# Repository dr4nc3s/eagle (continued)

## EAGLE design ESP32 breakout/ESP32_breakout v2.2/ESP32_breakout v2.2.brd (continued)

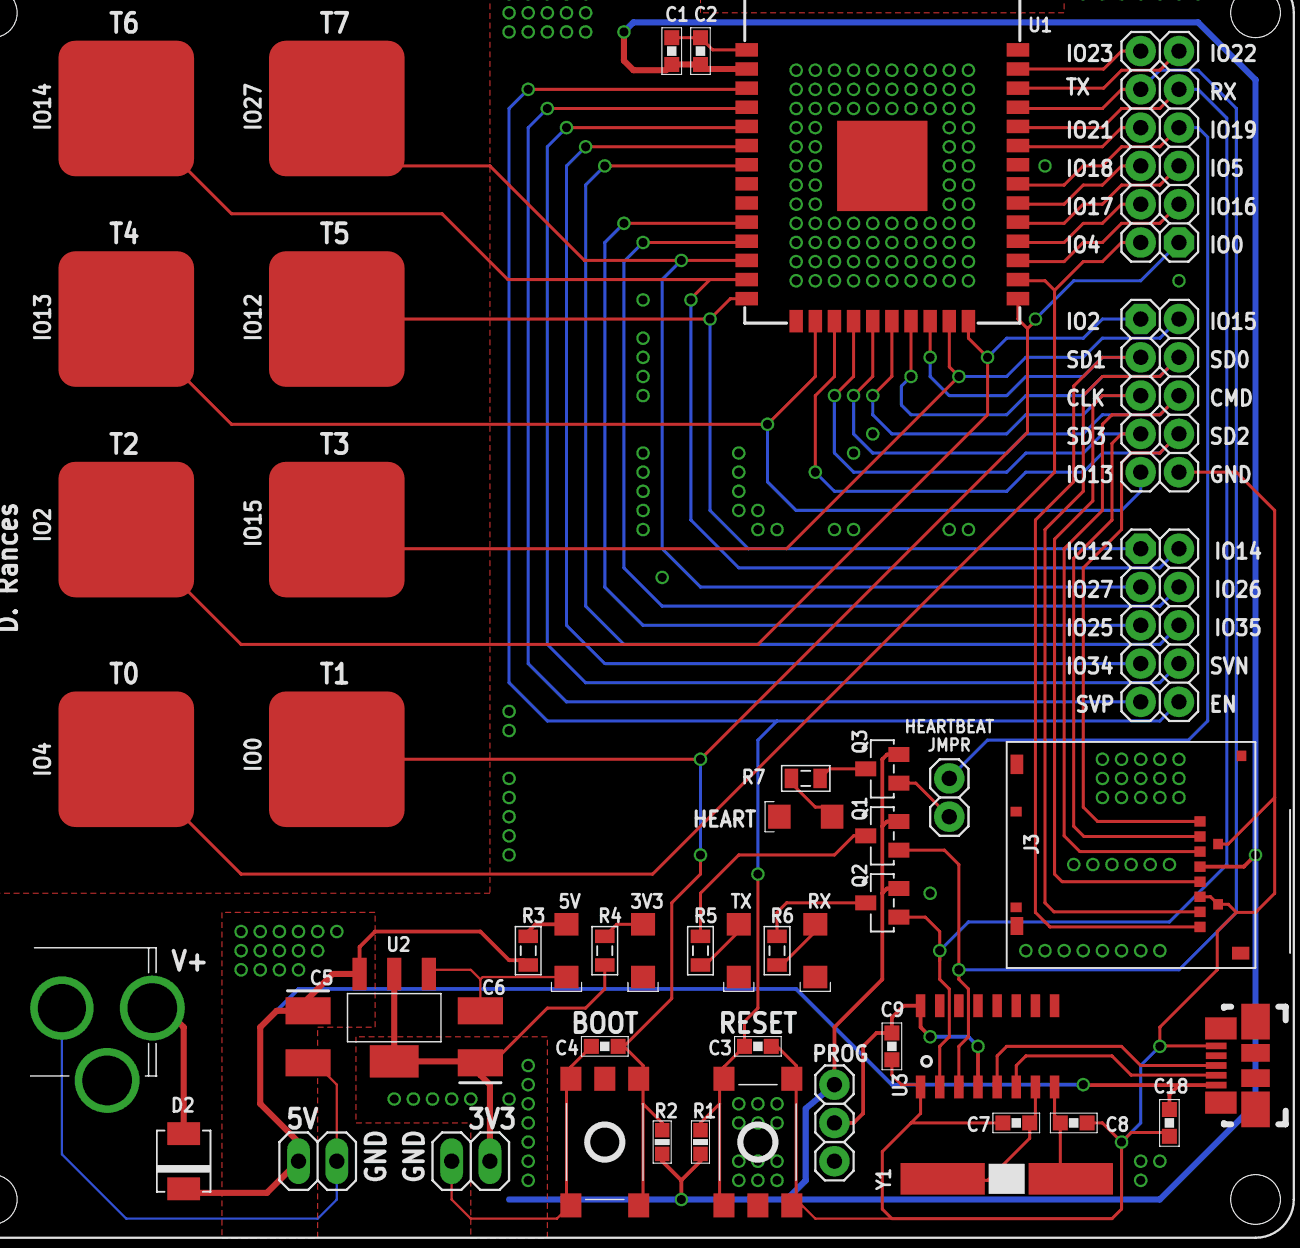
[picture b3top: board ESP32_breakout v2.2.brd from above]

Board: 2 copper layers, 54 parts (0 on the bottom side), 49 nets.

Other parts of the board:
U$2, U$6, U$10, U$11: STAND-OFF-HOLE

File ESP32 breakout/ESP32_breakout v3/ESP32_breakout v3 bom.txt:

Partlist exported from C:/Users/Mobile Me/Documents/GitHub/eagle/ESP32 breakout/ESP32_breakout v2.2/ESP32_breakout v2.2.sch at 6/23/2017 11:27 AM

Qty Value              Device               Package            Parts                                  Description                                             
1                      JACK-PLUG0           SPC4077            J1                                     DC POWER JACK                 ===                          
5                      LED1206              LED-1206           D1, D3, D4, D5, D6                                                   ===                          
2                      PUSHBUTTONSKHMQME010 SKHMQME010         S1, S2                                 ALPS Tactile Switch           ===                          
5   0.1uF              CAP0603              CAP-0603           C2, C3, C4, C9, C18                    Multilayer Ceramic Capacitor  ===                          
3   10k                RESISTOR0805         RES-0805           R1, R2, R8                                                            ===                         
2   10uF               CAP-POLARCASEB-3528  B-3528             C5, C6                                                               ===                          
1   10uF               CAP0603              CAP-0603           C1                                     Multilayer Ceramic Capacitor  ===                          
1   12MHz              ABLS-12MHZ-B2-T      HC-49/US           Y1                                     Abracon 12MHz Crystal          ===                         
2   22pF               CAP0805              CAP-0805           C7, C8                                 Multilayer Ceramic Capacitor  ===                          
5   330                RESISTOR0805         RES-0805           R3, R4, R5, R6, R7                                                   ===                          
3   BSS84              BSS84                SOT-23-3           Q1, Q2, Q3                             Fairchild Semiconductor       ===                          
1   CH340G             CH340G               SOIC16             U$7                                                                  ===                          
1   ESP-WROOM-32       ESP-WROOM-32         ESP-WROOM-32       U1                                                                   ===                          
1   JUMPER_2-WAY       JUMPER_2-WAY         1X02               JP6                                                                                            
2   M02LONG            M02LONG              1X02-LONG          JP4, JP5                                                                                       
2   M102X05            M102X05              2X05               JP2, JP3                                                                                       
1   M122ROWS           M122ROWS             2X06               JP1                                                                                            
1   MOLEX_USBMICRO     MOLEX_USBMICRO       MOLEX_47346-001    U$4                                                                                            
1   NCP-1117223-3      NCP-1117223-3        SOT-223-3          U2                                     ON Semiconductor Low Dropout Positive Voltage Regulator 
1   SCHA4B0419         SCHA4B0419           MICROSD_SCHA4B0419 J3                                     ALPS MicroSD Connector                                  
1   SPDT               SPDT                 1X03               S3                                                                                             
8   TOUCHPAD-10MMX10MM TOUCHPAD-10MMX10MM   TOUCH-10MMX10MM    C10, C11, C12, C13, C14, C15, C16, C17                                                         
1   VS-10BQ030-M3      VS-10BQ030-M3        DO-214AA           D2                                     Vishay Semiconductors

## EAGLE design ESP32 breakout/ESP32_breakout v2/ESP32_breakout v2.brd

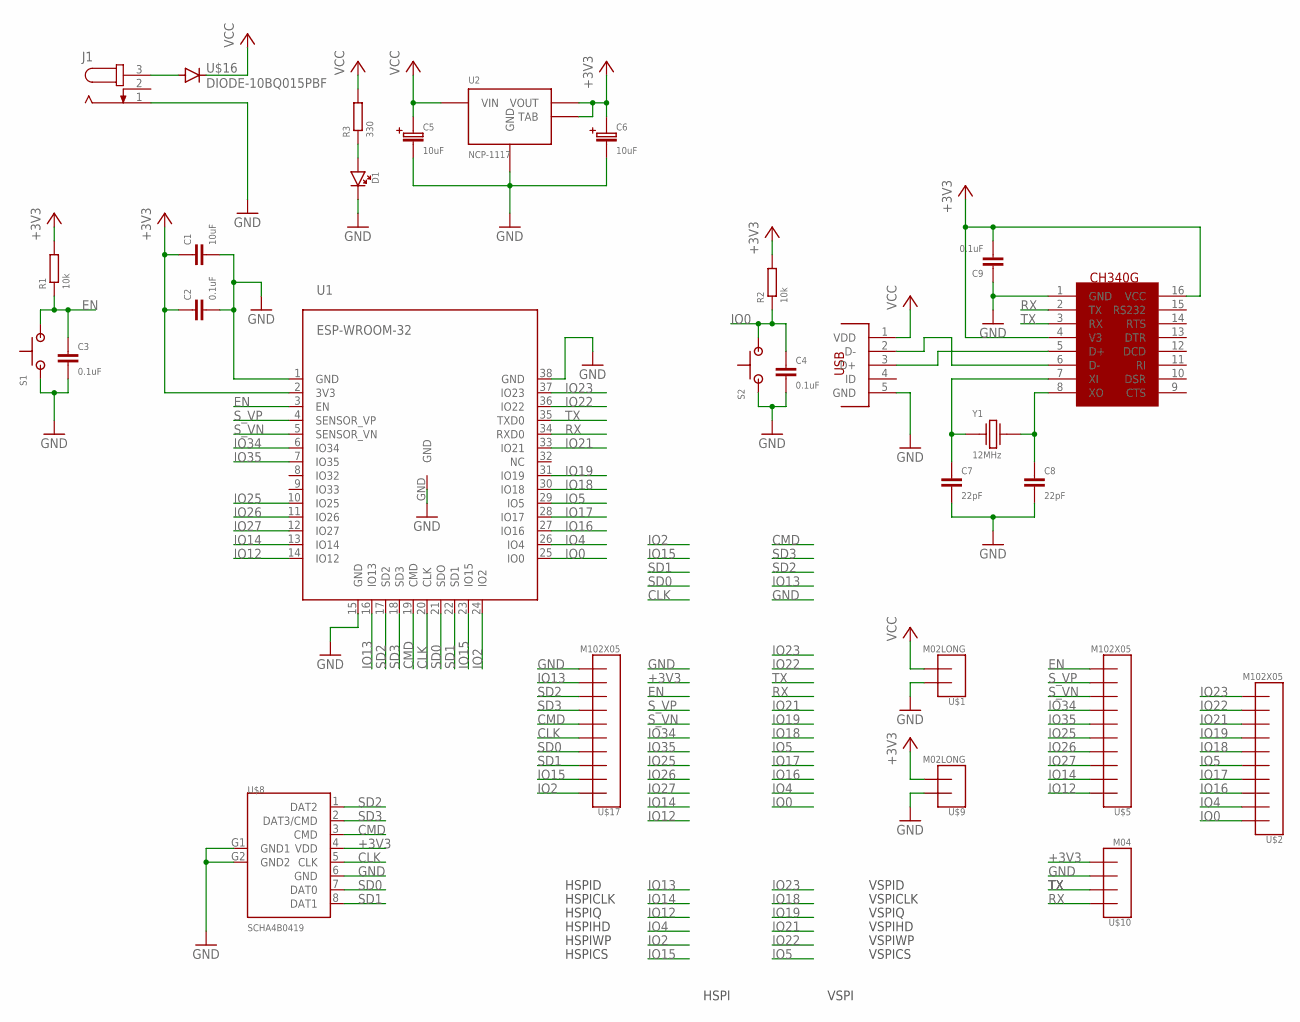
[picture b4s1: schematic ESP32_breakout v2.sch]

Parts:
C1: 10uF; CAP-0603
C2, C3, C4, C9: 0.1uF; CAP-0603
C5, C6: 10uF; B-3528
C7, C8: 22pF; CAP-0603
D1: LED1206; LED-1206
J1: JACK-PLUG0; SPC4077
R1, R2: 10k; RES-0603
R3: 330; RES-0603
S1, S2: PUSHBUTTONSKHMQME010; SKHMQME010
U1: ESP-WROOM-32
U2: NCP-1117; SOT-223-4
U$1, U$9: M02LONG; 1X02-LONG
U$2, U$5, U$17: M102X05; 2X05
U$4: MOLEX_USBMICRO; MOLEX_47346-001
U$7: CH340G; SOIC16
U$8: SCHA4B0419; MICROSD_SCHA4B0419
U$10: M04; 1X04
U$16: DIODE-10BQ015PBF; 10BQ015PB
Y1: 12MHz; HC-49/US

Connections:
+3V3: C1.1, C2.1, C6.P, C9.2, R1.2, R2.2, U1.2 (3V3), U2.2 (VOUT), U2.PAD (TAB), U$7.4 (V3), U$7.16 (VCC), U$8.4 (VDD), U$9.2, U$10.4
CLK: U1.20 (CLK), U$8.5 (CLK), U$17.5
CMD: U1.19 (CMD), U$8.3 (CMD), U$17.6
EN: C3.1, R1.1, S1.3 (2), S1.4 (2), U1.3 (EN), U$5.10
GND: C1.2, C2.2, C3.2, C4.2, C5.N, C6.N, C7.2, C8.2, C9.1, D1.C, J1.1, S1.1, S1.2 (1), S2.1, S2.2 (1), U1.1 (GND), U1.15 (GND), U1.38 (GND), U1.GND, U2.1 (GND), U$1.1, U$4.5 (GND), U$7.1 (GND), U$8.6 (GND), U$8.G1 (GND1), U$8.G2 (GND2), U$9.1, U$10.3, U$17.10
IO0: C4.1, R2.1, S2.3 (2), S2.4 (2), U1.25 (IO0), U$2.1
IO2: U1.24 (IO2), U$17.1
IO4: U1.26 (IO4), U$2.2
IO5: U1.29 (IO5), U$2.5
IO12: U1.14 (IO12), U$5.1
IO13: U1.16 (IO13), U$17.9
IO14: U1.13 (IO14), U$5.2
IO15: U1.23 (IO15), U$17.2
IO16: U1.27 (IO16), U$2.3
IO17: U1.28 (IO17), U$2.4
IO18: U1.30 (IO18), U$2.6
IO19: U1.31 (IO19), U$2.7
IO21: U1.33 (IO21), U$2.8
IO22: U1.36 (IO22), U$2.9
IO23: U1.37 (IO23), U$2.10
IO25: U1.10 (IO25), U$5.5
IO26: U1.11 (IO26), U$5.4
IO27: U1.12 (IO27), U$5.3
IO34: U1.6 (IO34), U$5.7
IO35: U1.7 (IO35), U$5.6
unnamed: D1.A, R3.1
unnamed 26: J1.3, U$16.A; also elsewhere on the board
unnamed: C7.1, U$7.7 (XI), Y1.P$1 (1)
unnamed: C8.1, U$7.8 (XO), Y1.P$2 (2)
unnamed: U$4.3 (D+), U$7.5 (D+)
unnamed: U$4.2 (D-), U$7.6 (D-)
RX: U1.34 (RXD0), U$7.2 (TX), U$10.1
SD0: U1.21 (SDO), U$8.7 (DAT0), U$17.4
SD1: U1.22 (SD1), U$8.8 (DAT1), U$17.3
SD2: U1.17 (SD2), U$8.1 (DAT2), U$17.8
SD3: U1.18 (SD3), U$8.2 (DAT3/CMD), U$17.7
S_VN: U1.5 (SENSOR_VN), U$5.8
S_VP: U1.4 (SENSOR_VP), U$5.9
TX: U1.35 (TXD0), U$7.3 (RX), U$10.2
VCC: C5.P, R3.2, U2.3 (VIN), U$1.2, U$4.1 (VDD), U$16.C; also elsewhere on the board

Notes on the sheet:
VSPI
HSPI
VSPID
VSPICLK
VSPIQ
VSPIHD
VSPIWP
VSPICS
HSPID
HSPICLK
HSPIQ
HSPIHD
HSPIWP
HSPICS

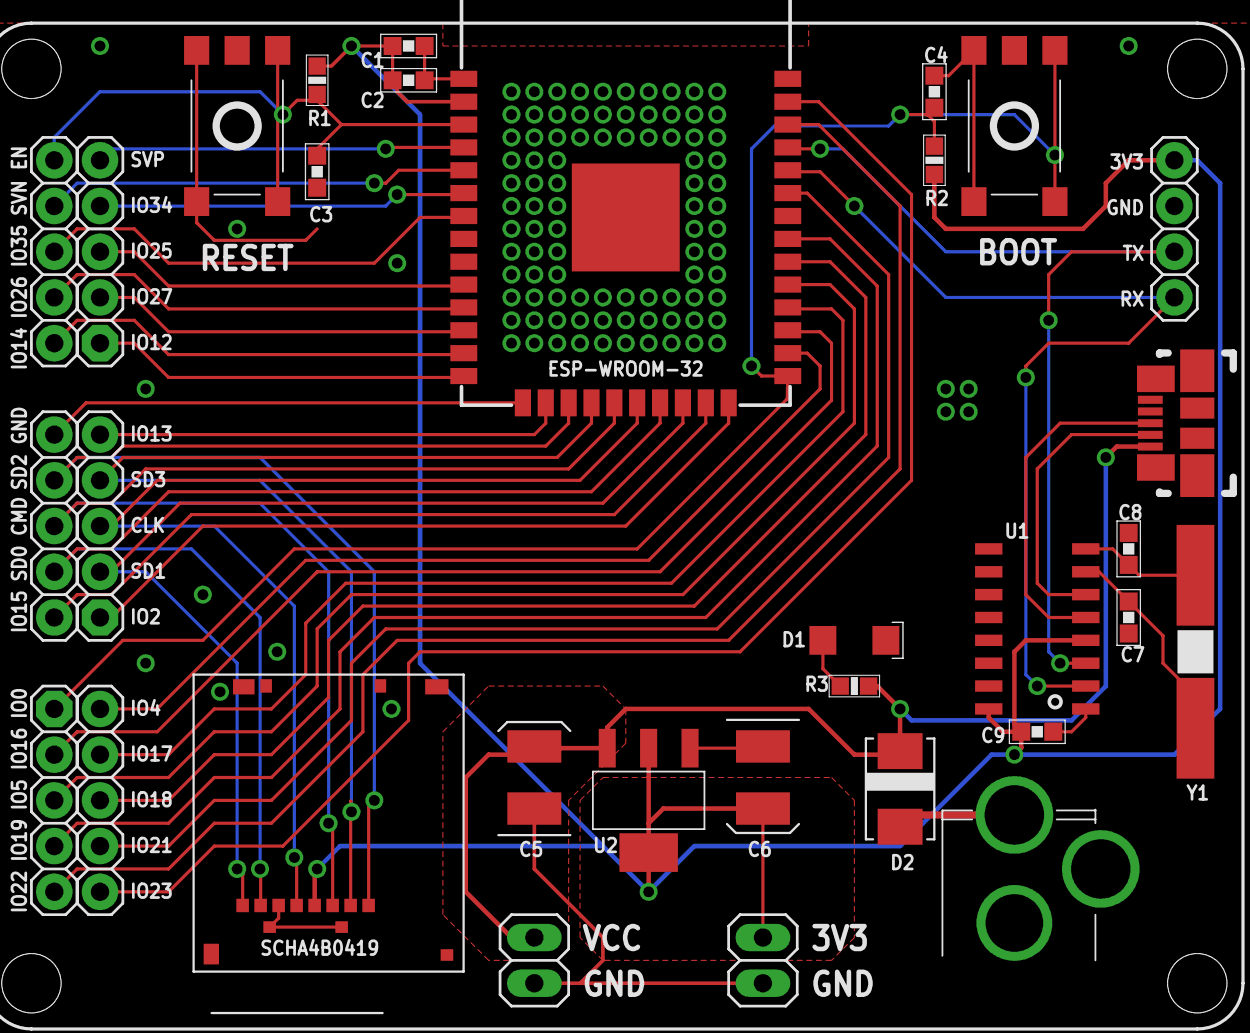
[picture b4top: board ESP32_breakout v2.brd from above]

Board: 2 copper layers, 33 parts (0 on the bottom side), 40 nets.

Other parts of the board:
D2: DIODE-10BQ015PBF; 10BQ015PB
U$3, U$6, U$14, U$15: STAND-OFF-HOLE

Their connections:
unnamed 26: D2.A; also elsewhere on the board
VCC: D2.C; also elsewhere on the board

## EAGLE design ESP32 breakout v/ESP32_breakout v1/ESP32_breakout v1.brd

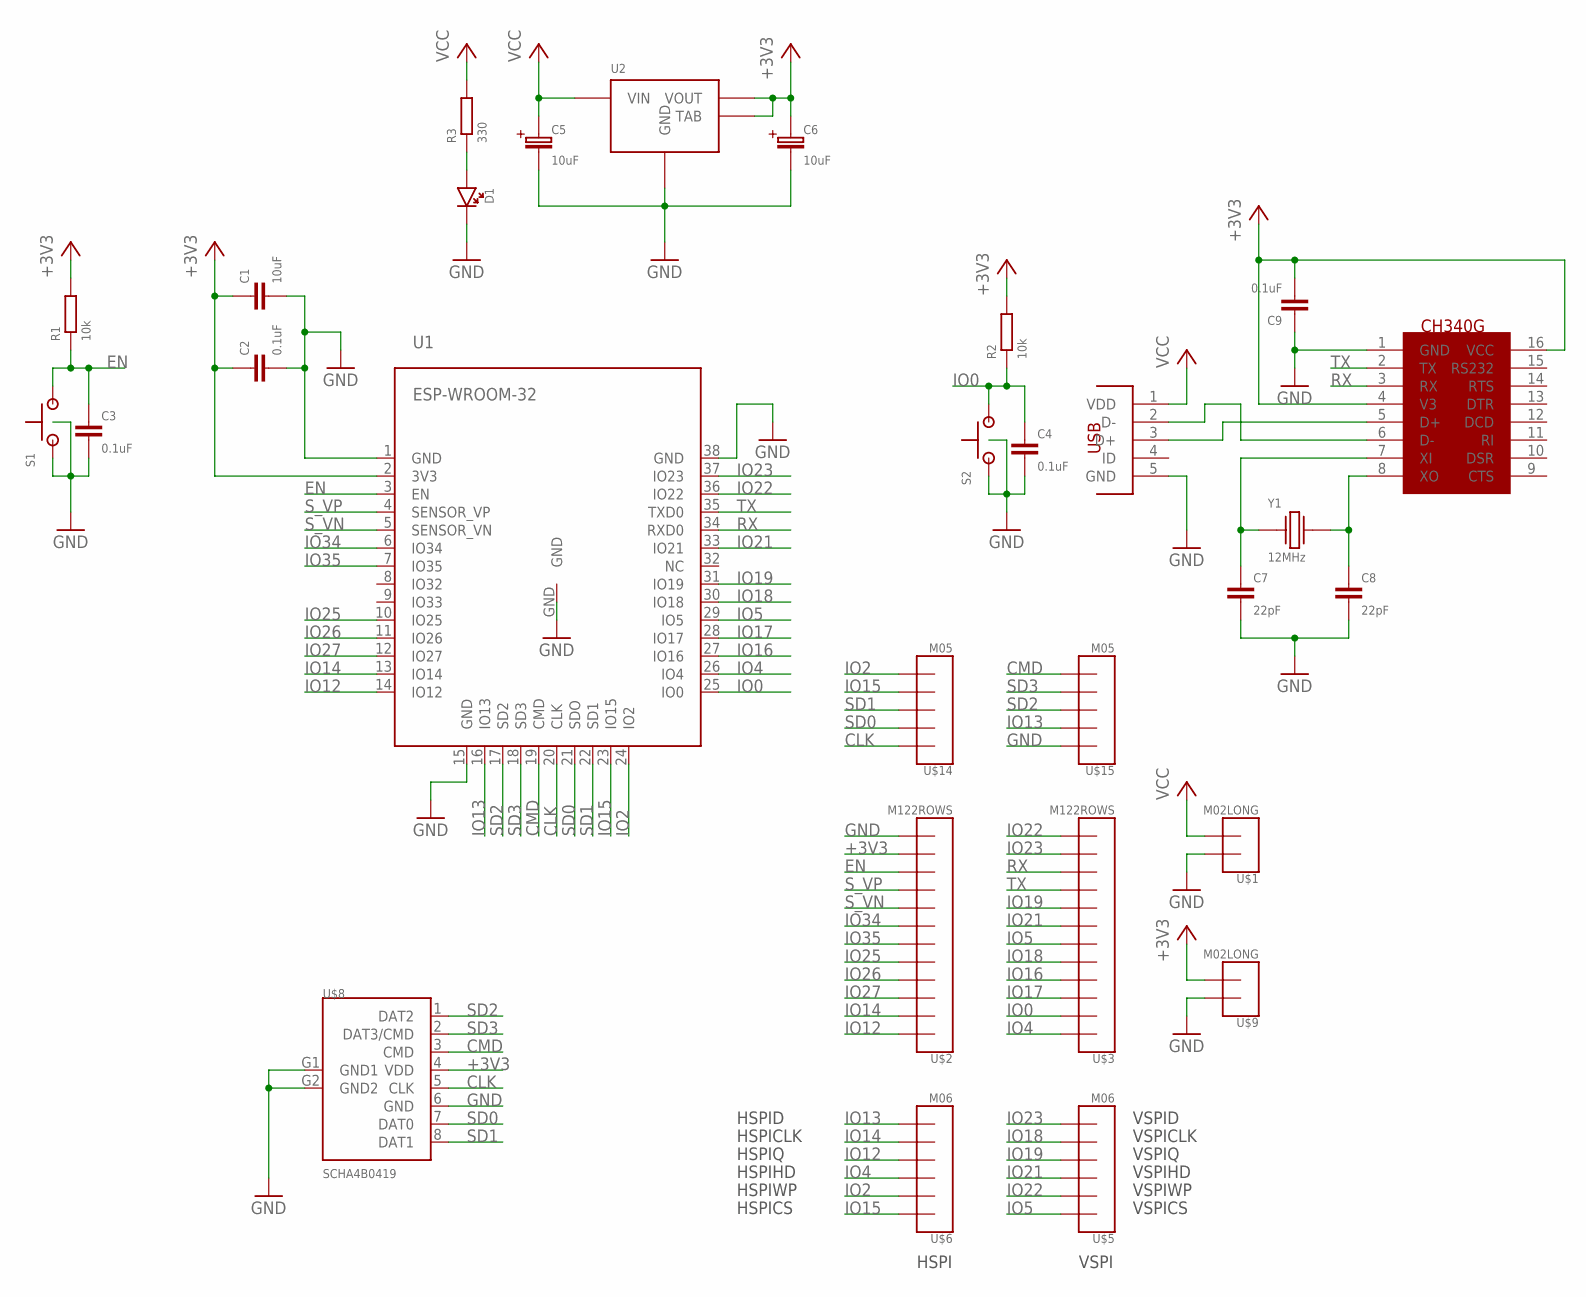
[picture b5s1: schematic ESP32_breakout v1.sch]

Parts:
C1: 10uF; CAP-0603
C2, C3, C4, C9: 0.1uF; CAP-0603
C5, C6: 10uF; B-3528
C7, C8: 22pF; CAP-0603
D1: LED1206; LED-1206
R1, R2: 10k; RES-0603
R3: 330; RES-0603
S1, S2: SKHMQME010
U1: ESP-WROOM-32
U2: NCP-1117; SOT-223-4
U$1, U$9: M02LONG; 1X02-LONG
U$2, U$3: M122ROWS; 2X06
U$4: MOLEX_USBMICRO; MOLEX_47346-001
U$5, U$6: M06; 1X06
U$7: CH340G; SOIC16
U$8: SCHA4B0419; MICROSD_SCHA4B0419
U$14, U$15: M05; 1X05
Y1: 12MHz; HC-49/US

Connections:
+3V3: C1.1, C2.1, C6.P, C9.2, R1.2, R2.2, U1.2 (3V3), U2.2 (VOUT), U2.PAD (TAB), U$2.11, U$7.4 (V3), U$7.16 (VCC), U$8.4 (VDD), U$9.2
CLK: U1.20 (CLK), U$8.5 (CLK), U$14.1
CMD: U1.19 (CMD), U$8.3 (CMD), U$15.5
EN: C3.1, R1.1, S1.3 (2), U1.3 (EN), U$2.10
GND: C1.2, C2.2, C3.2, C4.2, C5.N, C6.N, C7.2, C8.2, C9.1, D1.C, S1.1, S1.5 (3), S2.1, S2.5 (3), U1.1 (GND), U1.15 (GND), U1.38 (GND), U1.GND, U2.1 (GND), U$1.1, U$2.12, U$4.5 (GND), U$7.1 (GND), U$8.6 (GND), U$8.G1 (GND1), U$8.G2 (GND2), U$9.1, U$15.1
IO0: C4.1, R2.1, S2.3 (2), U1.25 (IO0), U$3.2
IO2: U1.24 (IO2), U$6.2, U$14.5
IO4: U1.26 (IO4), U$3.1, U$6.3
IO5: U1.29 (IO5), U$3.6, U$5.1
IO12: U1.14 (IO12), U$2.1, U$6.4
IO13: U1.16 (IO13), U$6.6, U$15.2
IO14: U1.13 (IO14), U$2.2, U$6.5
IO15: U1.23 (IO15), U$6.1, U$14.4
IO16: U1.27 (IO16), U$3.4
IO17: U1.28 (IO17), U$3.3
IO18: U1.30 (IO18), U$3.5, U$5.5
IO19: U1.31 (IO19), U$3.8, U$5.4
IO21: U1.33 (IO21), U$3.7, U$5.3
IO22: U1.36 (IO22), U$3.12, U$5.2
IO23: U1.37 (IO23), U$3.11, U$5.6
IO25: U1.10 (IO25), U$2.5
IO26: U1.11 (IO26), U$2.4
IO27: U1.12 (IO27), U$2.3
IO34: U1.6 (IO34), U$2.7
IO35: U1.7 (IO35), U$2.6
unnamed: D1.A, R3.1
unnamed: C7.1, U$7.7 (XI), Y1.P$1 (1)
unnamed: C8.1, U$7.8 (XO), Y1.P$2 (2)
unnamed: U$4.3 (D+), U$7.5 (D+)
unnamed: U$4.2 (D-), U$7.6 (D-)
RX: U1.34 (RXD0), U$3.10, U$7.3 (RX)
SD0: U1.21 (SDO), U$8.7 (DAT0), U$14.2
SD1: U1.22 (SD1), U$8.8 (DAT1), U$14.3
SD2: U1.17 (SD2), U$8.1 (DAT2), U$15.3
SD3: U1.18 (SD3), U$8.2 (DAT3/CMD), U$15.4
S_VN: U1.5 (SENSOR_VN), U$2.8
S_VP: U1.4 (SENSOR_VP), U$2.9
TX: U1.35 (TXD0), U$3.9, U$7.2 (TX)
VCC: C5.P, R3.2, U2.3 (VIN), U$1.2, U$4.1 (VDD)

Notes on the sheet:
VSPI
HSPI
VSPID
VSPICLK
VSPIQ
VSPIHD
VSPIWP
VSPICS
HSPID
HSPICLK
HSPIQ
HSPIHD
HSPIWP
HSPICS

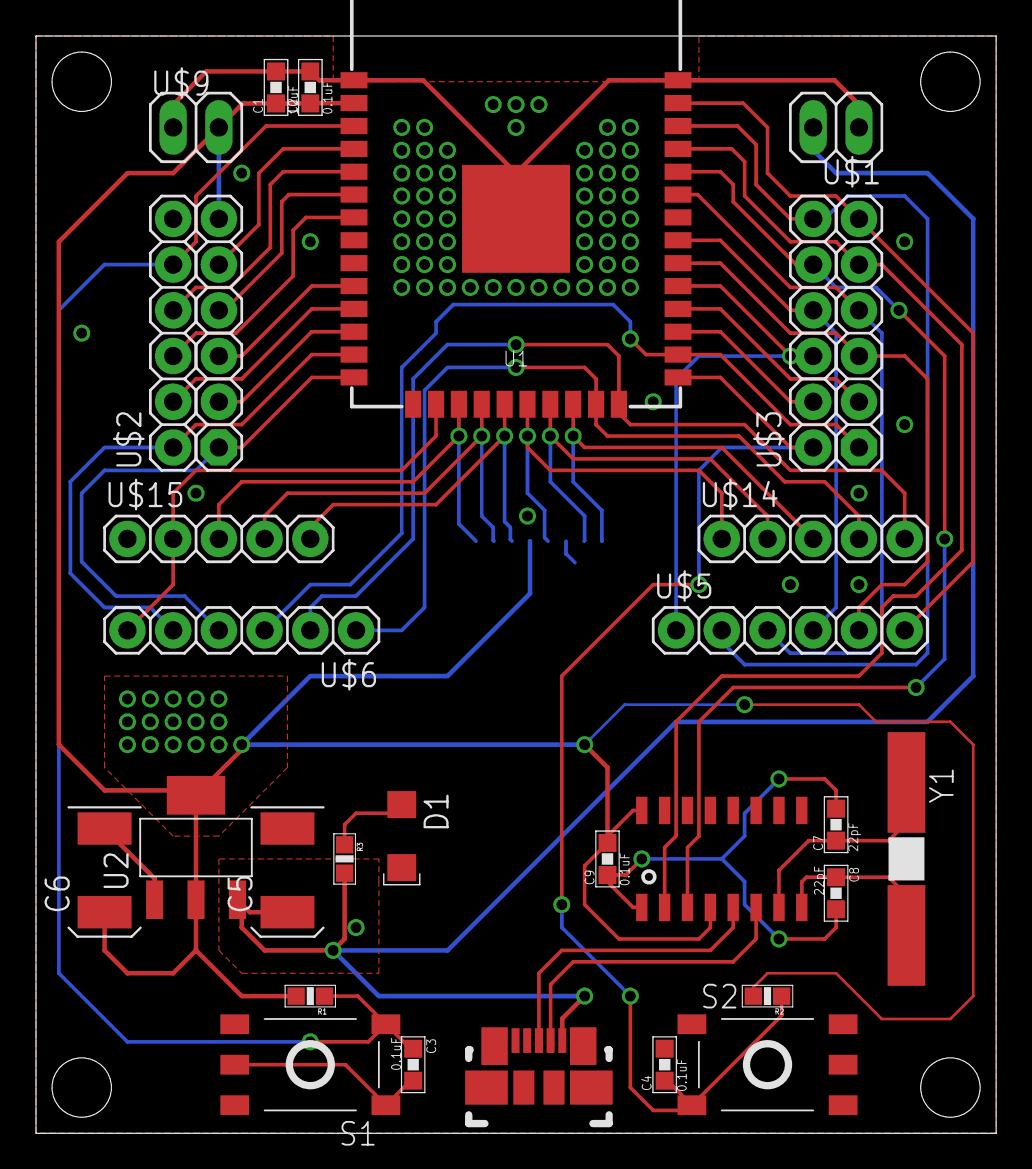
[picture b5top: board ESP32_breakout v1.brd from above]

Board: 2 copper layers, 53.3 x 61.0 mm, 33 parts (1 on the bottom side), 39 nets.

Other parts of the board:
U$10, U$11, U$12, U$13: STAND-OFF-HOLE

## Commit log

2017-04-17 :confetti_ball: Added .gitattributes & .gitignore files
2017-04-17 Added verification project
2017-04-17 Added library folder
2017-04-18 Edited packages
2017-04-18 Added new devices
2017-04-18 New project
2017-04-19 headers
2017-04-20 Added more parts
2017-04-20 Modified symbols
2017-04-24 New parts
2017-04-25 Added crystal
2017-04-28 More parts
2017-04-28 Some changes
2017-05-02 Added README
2017-05-03 ESP32 breakout started
2017-05-09 ESP32
2017-05-09 Write pins
2017-05-09 Header breakouts added
2017-05-09 Rough component placement
2017-05-10 Added USB ccomponents
2017-05-10 Added ALPS new microsd connector
2017-05-12 layout
2017-05-13 PCB layout
2017-05-13 ESP32 v1 done
2017-05-15 SAML21
2017-05-16 Finish layout
2017-05-16 Generate output files
2017-05-16 change
2017-05-20 Added ams CCS811 Indoor Gas Sensor package
2017-05-23 Added image
2017-06-05 Swtiched microUSB breakout
2017-06-05 Made rounded board. Modified component libraries
2017-06-05 Resized PCB v2
2017-06-05 Finished major traces
2017-06-05 Version 2, pre-check
2017-06-05 Added labels
2017-06-06 More vias
2017-06-06 Added external vref
2017-06-06 Added touchpad
2017-06-06 PCB with touchpad
2017-06-06 PCB touchpad
2017-06-07 Traces
2017-06-07 Added more status LEDs
2017-06-07 Layers
2017-06-08 Added USB bypass cap and extra status LED
2017-06-09 Modified labels
2017-06-12 Add 2nd status LED
2017-06-13 DRU check
2017-06-14 gerber generated
2017-06-15 Added switch for USB-UART
2017-06-16 Board layout started
2017-06-19 breakout
2017-06-20 component layout
2017-06-21 Added USB interface
2017-06-23 Component size change
2017-06-27 Parts
2017-09-01 Fixing conflicts
2017-09-01 Added SAML21 v2
2017-09-01 Layout and 80% routing done
2017-09-05 Generated gerber
2017-09-08 v3 routing
2017-09-10 Finished tracing part 2
2017-09-11 PCB made
2017-09-12 Edit Zigbee S2C
2017-09-14 Added TLC5971
2017-09-14 Printout of Xbee
2017-09-19 Added LED for microSD CD
2017-09-19 Generate gerber files
2017-09-19 SMT Header
2017-09-21 Modified slide switch spdt
2017-10-02 Project file without touchpads
    Strictly for stencil generation
2018-01-10 Added PMOS version
